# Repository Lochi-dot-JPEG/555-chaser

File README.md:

# Strawberry 555 Chaser

A strawberry themed 555 chaser blinky, that flashes 10 leds in a circle using a timer and counter circuit.

Made from [this hackclub tutorial](https://stasis.hackclub.com/starter-projects/blinky).

I made this project as an exercise to learn how to design pcbs using kicad. I learnt how to create schematics and design a pcb ready for manufacturing.

## Bill of Materials

| Item | Amount |
| - | - |
| pcb | 1 |
| led | 10 |
| NE555P | 1 |
| Conn 1x2 socket | 1 |
| Conn 1x1 socket | 1 |
| 1k ohm resistor | 1 |
| 470 ohm resistor | 1 |
| Potentiometer | 1 |
| Capacitor (0.01 uF) | 1 |
| Electrolytic capacitor (1 uF) | 1 |
| CD4017 | 1 |

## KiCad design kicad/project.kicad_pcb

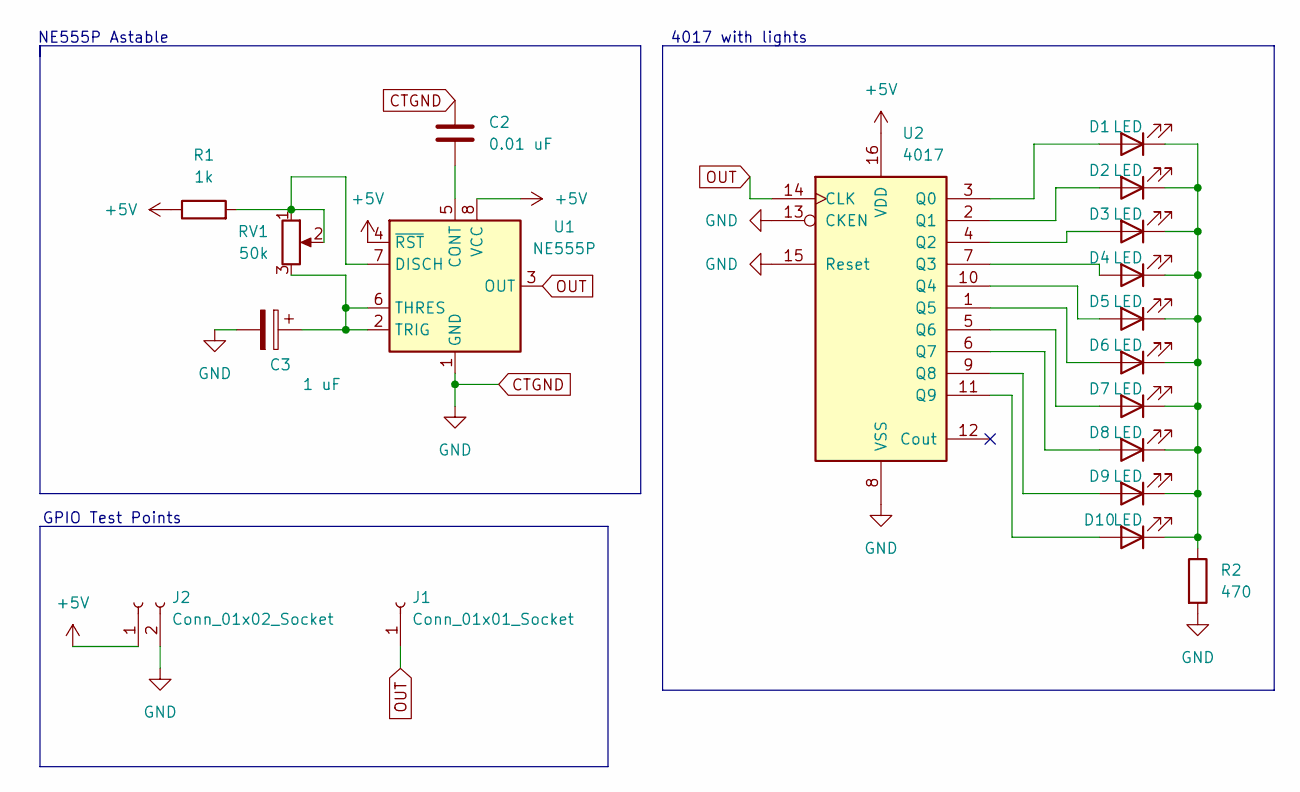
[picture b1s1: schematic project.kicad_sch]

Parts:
C2: 0.01 uF; C_Disc_D7.5mm_W2.5mm_P5.00mm
C3: 1 uF; CP_Radial_D5.0mm_P2.00mm
D1, D2, D3, D4, D5, D6, D7, D8, D9, D10: LED; LED_D3.0mm
J1: Conn_01x01_Socket; PinHeader_1x01_P2.54mm_Vertical
J2: Conn_01x02_Socket; PinHeader_1x02_P2.54mm_Vertical
R1: 1k; R_Axial_DIN0207_L6.3mm_D2.5mm_P7.62mm_Horizontal
R2: 470; R_Axial_DIN0207_L6.3mm_D2.5mm_P7.62mm_Horizontal
RV1: 50k; Potentiometer_Vishay_T93YA_Vertical
U1: NE555P; DIP-8_W7.62mm
U2: 4017; DIP794W45P254L1969H508Q16

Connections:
+5V: J2.1, R1.1, U1.4 (~RST), U1.8 (VCC), U2.16 (VDD)
CTGND: C2.1, C3.2, J2.2, R2.2, U1.1 (GND), U2.8 (VSS), U2.13 (CKEN), U2.15 (Reset)
unnamed: D1.2 (A), U2.3 (Q0)
unnamed: D1.1 (K), D2.1 (K), D3.1 (K), D4.1 (K), D5.1 (K), D6.1 (K), D7.1 (K), D8.1 (K), D9.1 (K), D10.1 (K), R2.1
unnamed: D2.2 (A), U2.2 (Q1)
unnamed: D3.2 (A), U2.4 (Q2)
unnamed: D4.2 (A), U2.7 (Q3)
unnamed: D5.2 (A), U2.10 (Q4)
unnamed: D6.2 (A), U2.1 (Q5)
unnamed: D7.2 (A), U2.5 (Q6)
unnamed: D8.2 (A), U2.6 (Q7)
unnamed: D9.2 (A), U2.9 (Q8)
unnamed: D10.2 (A), U2.11 (Q9)
unnamed: C2.2, U1.5 (CONT)
unnamed: R1.2, RV1.1, RV1.2, U1.7 (DISCH)
unnamed: C3.1, RV1.3, U1.2 (TRIG), U1.6 (THRES)
OUT: J1.1 (Pin_1_1), U1.3 (OUT), U2.14 (CLK)

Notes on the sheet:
NE555P Astable
GPIO Test Points
4017 with lights

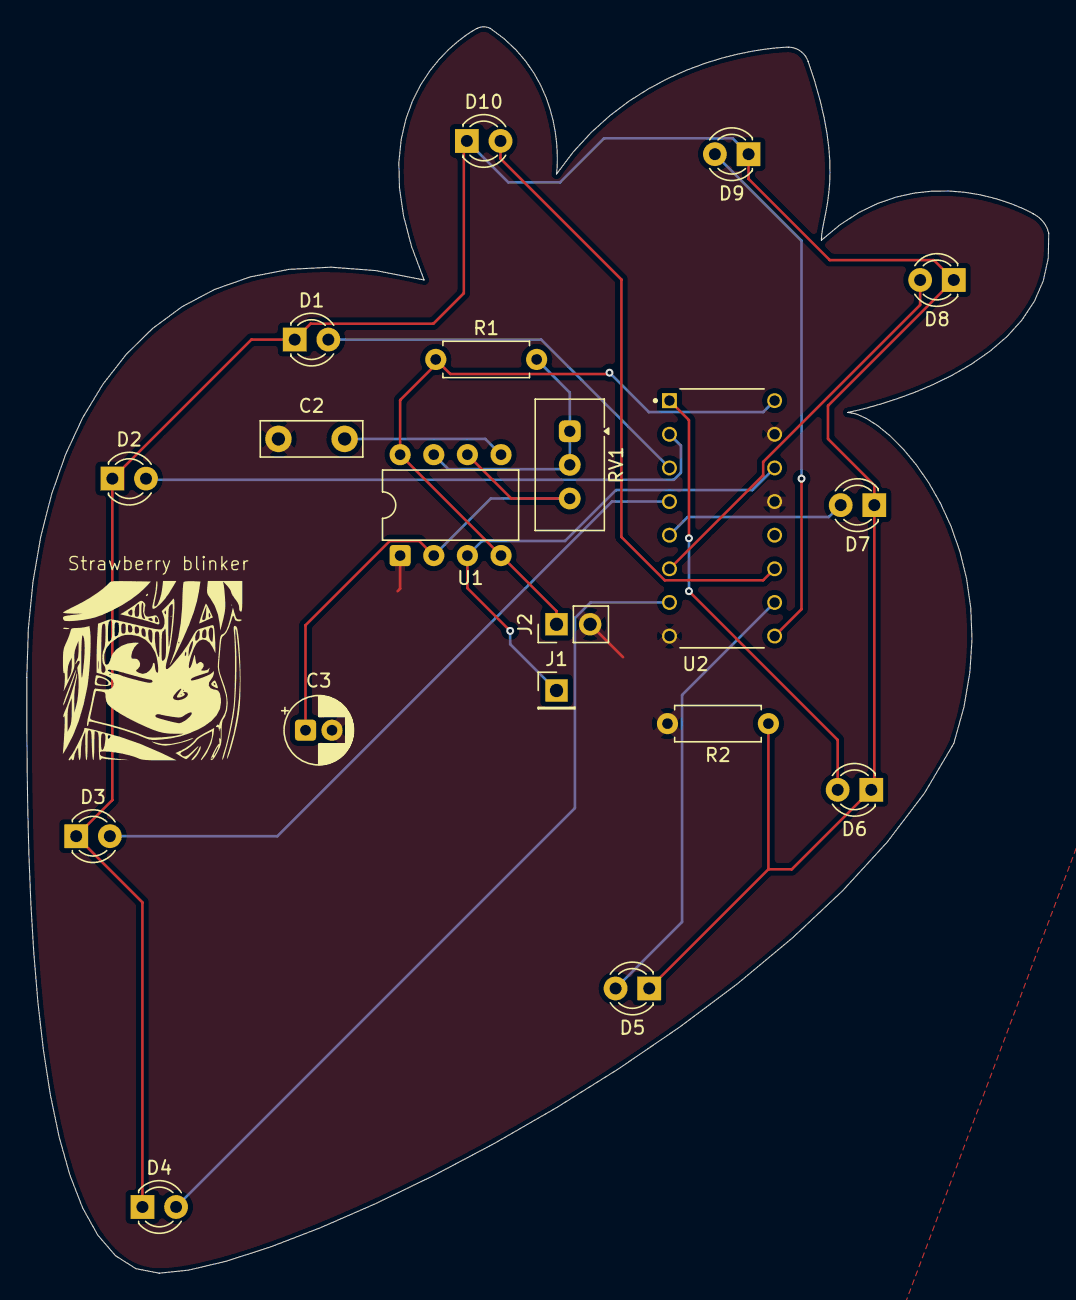
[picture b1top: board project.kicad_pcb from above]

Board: 2 copper layers, 77.2 x 94.1 mm, 19 parts (0 on the bottom side), 17 nets.

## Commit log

2026-04-18 add readme
2026-04-18 project files
2026-04-19 fix: correctly ordered lights
